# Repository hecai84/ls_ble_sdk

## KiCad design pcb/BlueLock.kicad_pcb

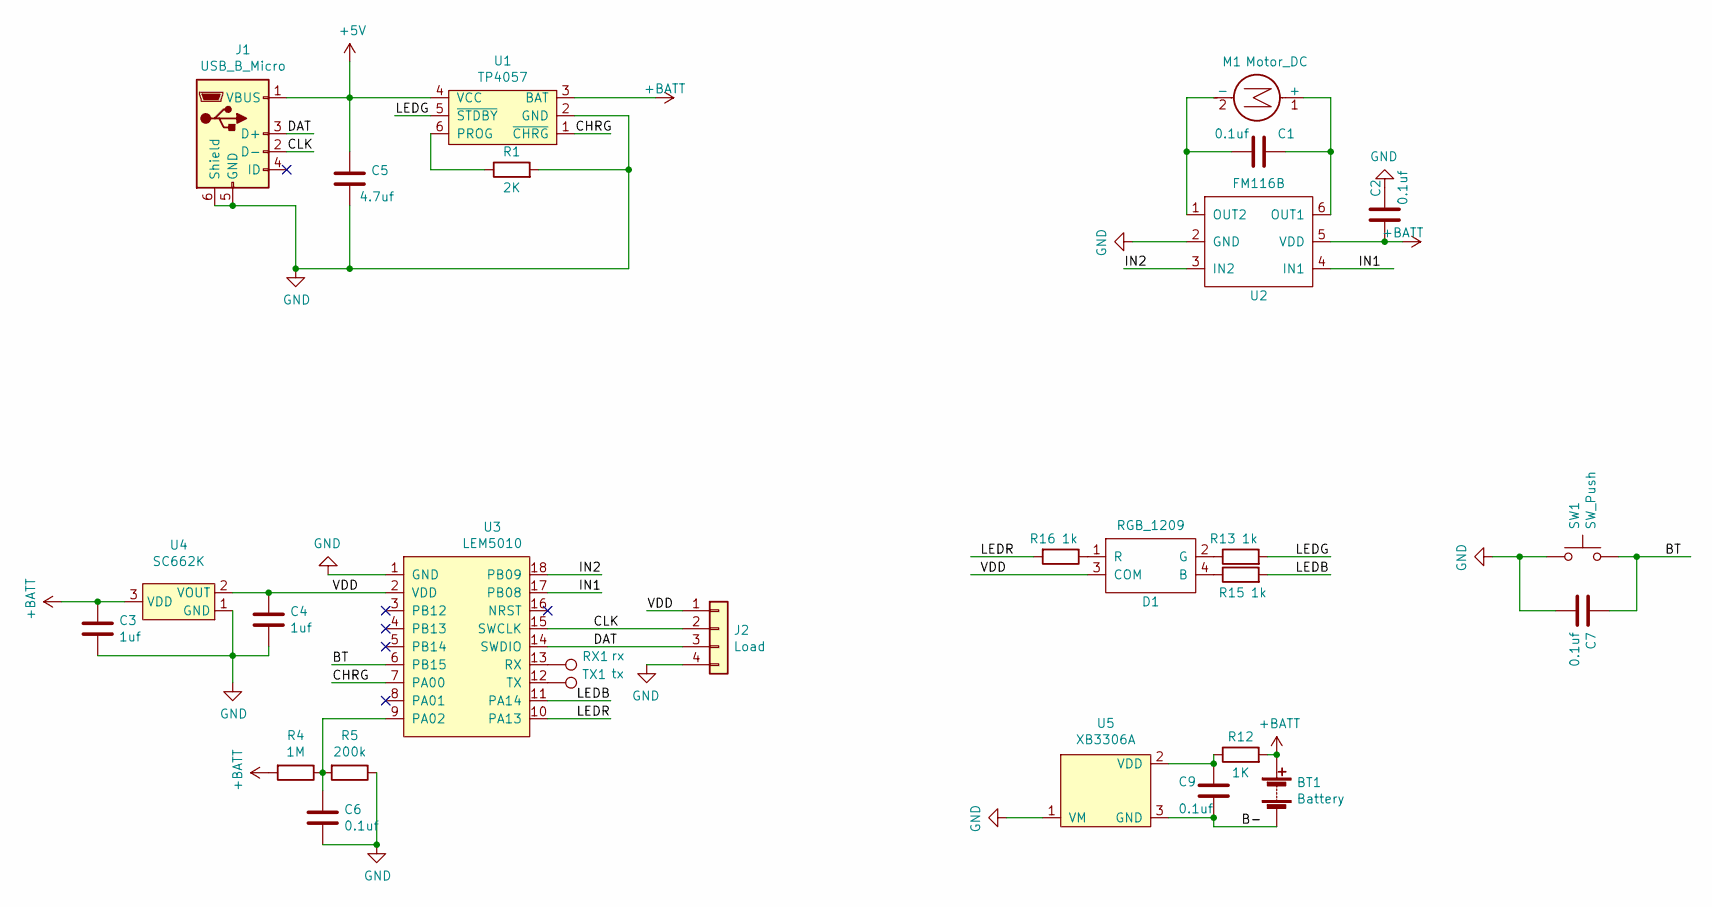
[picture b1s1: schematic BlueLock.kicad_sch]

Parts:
BT1: Battery; Pin_2_wide
C1, C2, C6, C7, C9: 0.1uf; C_0603_1608Metric
C3, C4: 1uf; C_0603_1608Metric
C5: 4.7uf; C_0603_1608Metric
D1: RGB_1209
J1: USB_B_Micro; USB_Micro-B_Molex-105017-0001
J2: Load; PinHeader_1x04_P2.54mm_Vertical
M1: Motor_DC; Pin_2_wide
R1: 2K; R_0603_1608Metric
R4: 1M; R_0603_1608Metric
R5: 200k; R_0603_1608Metric
R12: 1K; R_0603_1608Metric
R13, R15, R16: 1k; R_0603_1608Metric
RX1: rx; TestPoint_Pad_1.0x1.0mm
SW1: SW_Push; SW_6x6
TX1: tx; TestPoint_Pad_1.0x1.0mm
U1: TP4057; SOT-23-6
U2: FM116B; SOT-23-6
U3: LEM5010
U4: SC662K; SOT-23
U5: XB3306A; SOT-23

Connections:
+5V: C5.1, J1.1 (VBUS), U1.4 (VCC)
+BATT: BT1.1 (+), C2.1, C3.1, R4.2, R12.2, U1.3 (BAT), U2.5 (VDD), U4.3 (VDD)
/B-: BT1.2 (-), C9.2, U5.3 (GND)
/BT: C7.1, SW1.2, U3.6 (PB15)
/CHRG: U1.1 (~CHRG), U3.7 (PA00)
/CLK: J1.2 (D-), J2.2, U3.15 (SWCLK)
/DAT: J1.3 (D+), J2.3, U3.14 (SWDIO)
/IN1: U2.4 (IN1), U3.17 (PB08)
/IN2: U2.3 (IN2), U3.18 (PB09)
/LEDB: R15.2, U3.11 (PA14)
/LEDG: R13.2, U1.5 (~STDBY)
/LEDR: R16.2, U3.10 (PA13)
/VDD: C4.1, D1.3 (COM), J2.1, U3.2 (VDD), U4.2 (VOUT)
GND: C2.2, C3.2, C4.2, C5.2, C6.2, C7.2, J1.5 (GND), J1.6 (Shield), J2.4, R1.2, R5.1, SW1.1, U1.2 (GND), U2.2 (GND), U3.1 (GND), U4.1 (GND), U5.1 (VM)
unnamed: C1.1, M1.1 (+), U2.6 (OUT1)
unnamed: C1.2, M1.2 (-), U2.1 (OUT2)
unnamed: C6.1, R4.1, R5.2, U3.9 (PA02)
unnamed: C9.1, R12.1, U5.2 (VDD)
unnamed: D1.1 (R), R16.1
unnamed: D1.2 (G), R13.1
unnamed: D1.4 (B), R15.1
unnamed: R1.1, U1.6 (PROG)
unnamed: RX1.1, U3.13 (RX)
unnamed: TX1.1, U3.12 (TX)

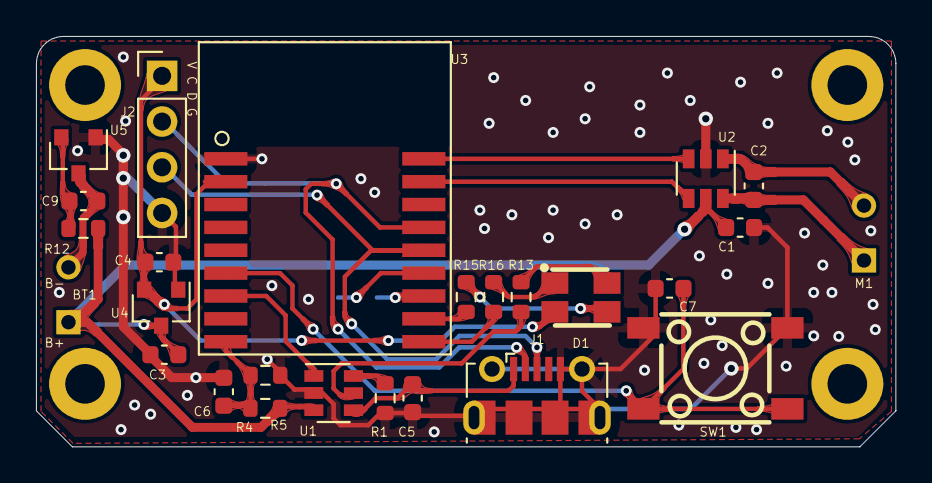
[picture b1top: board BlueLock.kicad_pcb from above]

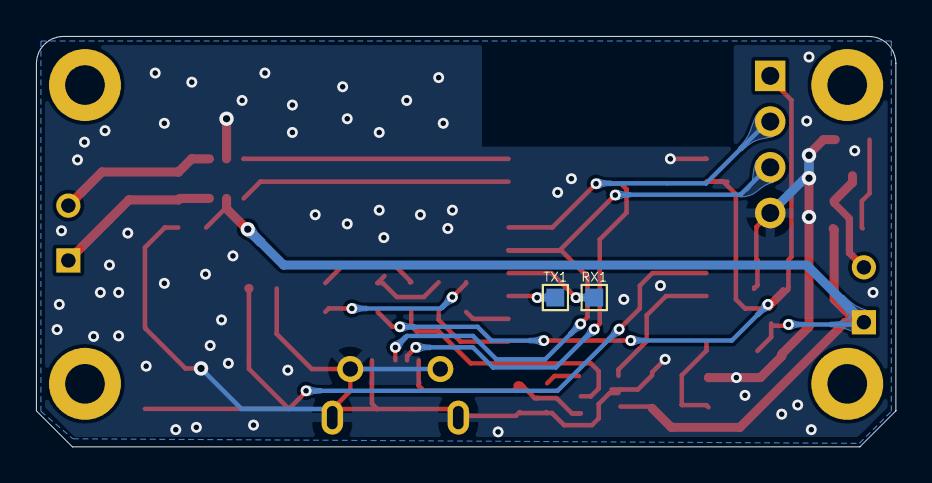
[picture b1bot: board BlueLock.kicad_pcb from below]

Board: 2 copper layers, 47.7 x 22.8 mm, 32 parts (2 on the bottom side), 24 nets.

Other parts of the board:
0, 0#2, 0#3, 0#4: R2R4

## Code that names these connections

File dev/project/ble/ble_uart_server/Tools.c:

/*
 * @Description:
 * @Author: hecai
 * @Date: 2021-09-16 10:44:14
 * @LastEditTime: 2023-03-15 11:43:16
 * @FilePath: \ls_ble_sdk\dev\project\ble\ble_uart_server\Tools.c
 */
#include "Tools.h"
#include "lscrypt.h"
#include "lsadc.h"
#include <string.h>
#include "flash.h"
/**buff**/
uint8_t ciphertext_buff[64];
uint8_t plaintext_buff[64];
extern u8 pw[];
extern u8 lastTime[];

#define BT PB15
#define CHRG PA00
#define LED_RED PA14
#define LED_BLUE PA13
#define TWINK_BLUE_TIME 500
#define TWINK_RED_TIME1 500
#define TWINK_RED_TIME2 1500
#define LONGPRESS_TIME 3000
#define CHRG_OVERTIME 500
#define REFRESH_VBAT_TIME 60000

static struct builtin_timer *led_timer_blue = NULL;
static struct builtin_timer *led_timer_red = NULL;
static struct builtin_timer *click_timer = NULL;
static struct builtin_timer *chrg_timer = NULL;
static u8 twinkRedTimes;
static u8 twinkBlueTimes;
volatile uint8_t recv_flag = 1;
ADC_HandleTypeDef hadc;
u8 battery = 5;
u8 redState = 1;
#include "main.h"

void Error_Handler(void);

void initLed(void)
{
    io_cfg_output(LED_RED); // LEDR
    // io_cfg_opendrain(LED_RED);
    io_write_pin(LED_RED, 1);
    io_cfg_output(LED_BLUE); // LEDB
    // io_cfg_opendrain(LED_BLUE);
    io_write_pin(LED_BLUE, 1);
}

/*
在LE501X系统中，只有PA00、PA07、PB11、PB15四个IO可以在任
意状态下触发中断，其余IO只能在CPU工作状态下触发中断，不能在BLE休眠状态下触发中断。
BLE处于广播或者连接时，系统根据广播、连接的间隔定期自动休眠、唤醒，所以这种应用场景，
建议使用上述四根IO作为中断。
*/
void initExti(void)
{
    io_cfg_input(BT);                     // PB11 config input
    io_pull_write(BT, IO_PULL_UP);        // PB11 config pullup
    io_exti_config(BT, INT_EDGE_FALLING); // PB11 interrupt falling edge
    io_exti_enable(BT, true);             // PB11 interrupt enable

    io_cfg_input(CHRG);                     // PB11 config input
    io_pull_write(CHRG, IO_PULL_UP);        // PB11 config pullup
    io_exti_config(CHRG, INT_EDGE_FALLING); // PB11 interrupt falling edge
    io_exti_enable(CHRG, true);             // PB11 interrupt enable
}

void toggleRed(void *param)
{
    if (twinkRedTimes != 255)
        twinkRedTimes--;
    redState = !redState;
    io_write_pin(LED_RED, redState);
    if (led_timer_red && twinkRedTimes > 0)
    {
        if (redState == 0)
        {
            builtin_timer_start(led_timer_red, TWINK_RED_TIME1, NULL);
        }
        else
        {
            builtin_timer_start(led_timer_red, TWINK_RED_TIME2, NULL);
        }
    }
}
void toggleBlue(void *param)
{
    twinkBlueTimes--;
    io_toggle_pin(LED_BLUE);
    if (led_timer_blue && twinkBlueTimes > 0)
    {
        builtin_timer_start(led_timer_blue, TWINK_BLUE_TIME, NULL);
    }
    else
    {
        io_write_pin(LED_BLUE, 1);
    }
}
void longPress(void *param)
{
    if (io_read_pin(BT) == 0)
    {
        LOG_I("longPress");
        SetLedBlue(LED_TWINK);
        memcpy(pw, DEFAULT_PW, 16);
        LOG_I("new pw:%s", pw);
        memset(lastTime, 0, 11);
        writeFlash(RECODE_PW, pw, 16);
    }
}
void chrgcheck(void *param)
{
    if (io_read_pin(CHRG) == 0)
    {
        SetLedRed(LED_OPEN);
        if (chrg_timer)
            builtin_timer_start(chrg_timer, CHRG_OVERTIME, NULL);
    }
    else
    {
        LOG_I("charge out");
        UpdateBattery();
        updateAdv();
        SetLedRed(LED_CLOSE);
    }
}

void lsadc_init(void)
{
    /** Common config  */
    hadc.Instance = LSADC;
    hadc.Init.DataAlign = ADC_DATAALIGN_RIGHT;
    hadc.Init.ScanConvMode = ADC_SCAN_DISABLE; /* Sequencer disabled (ADC conversion on only 1 channel: channel set on rank 1) */
    hadc.Init.NbrOfConversion = 1;             /* Parameter discarded because sequencer is disabled */
    hadc.Init.DiscontinuousConvMode = DISABLE; /* Parameter discarded because sequencer is disabled */
    hadc.Init.NbrOfDiscConversion = 1;         /* Parameter discarded because sequencer is disabled */

    hadc.Init.ContinuousConvMode = ENABLE;           /* Continuous mode to have maximum conversion speed (no delay between conversions) */
    hadc.Init.TrigType = ADC_REGULAR_SOFTWARE_TRIGT; /* Trig of conversion start done by which event */
    hadc.Init.Vref = ADC_VREF_INSIDE;
}

void HAL_ADC_ConvCpltCallback(ADC_HandleTypeDef *h)
{
    u16 value;
    // 1400/4095*6
    value = HAL_ADC_GetValue(h) * 2.051;
    LOG_I("battery:%d", value);
    if (value < 3200)
    {
        LOG_I("twink red");
        SetLedRed(LED_TWINK);
    }
    else if (io_read_pin(CHRG) != 0)
    {
        SetLedRed(LED_CLOSE);
    }
    // 3*1400*adc_value/4095
    if (value > 3950)
        battery = 5;
    else if (value > 3800)
        battery = 4;
    else if (value > 3600)
        battery = 3;
    else if (value > 3400)
        battery = 2;
    else
        battery = 1;
    recv_flag = 1;
    adc12b_in6_io_deinit();
    HAL_ADC_Stop_IT(h); // close adc per
    HAL_ADC_DeInit(h);
    //如果电量有变化，重新检查是否有变化
}

void UpdateBattery(void)
{
    if (1)
    {
        if (HAL_ADC_Init(&hadc) != HAL_OK)
        {
            LOG_I("HAL_ADC_Init error");
            Error_Handler();
        }

        ADC_ChannelConfTypeDef sConfig = {0};
        /**
         * Configure Regular Channel
         */
        sConfig.Channel = ADC_CHANNEL_6;
        sConfig.Rank = ADC_REGULAR_RANK_1;
        sConfig.SamplingTime = 0x00000002U;
        if (HAL_ADC_ConfigChannel(&hadc, &sConfig) != HAL_OK)
        {
            Error_Handler();
        }
        adc12b_in6_io_init();
        recv_flag = 0;
        LOG_I("HAL_ADC_Start_IT");
        HAL_ADC_Start_IT(&hadc);
    }

    // if (recv_flag == 1)
    // {
    //     recv_flag = 0;
    //     HAL_ADC_Start_IT(&hadc);
    // }
}

void SetLedRed(LED_STATE state)
{
    twinkRedTimes = 255;
    if (state == LED_TWINK)
    {
        LOG_I("SetLedRed TWINK");
        if (led_timer_red == NULL)
        {
            led_timer_red = builtin_timer_create(toggleRed);
        }
        io_write_pin(LED_RED, 0);
        redState = 0;
        LOG_I("star SetLedRed TWINK");
        builtin_timer_start(led_timer_red, 500, NULL);
    }
    else
    {
        if (led_timer_red != NULL)
        {
            builtin_timer_stop(led_timer_red);
        }
        if (state == LED_OPEN)
            io_write_pin(LED_RED, 0);
        if (state == LED_CLOSE)
            io_write_pin(LED_RED, 1);
    }
}

void SetLedBlue(LED_STATE state)
{
    if (state == LED_TWINK)
    {
        twinkBlueTimes = 10;
        LOG_I("SetLedBlue TWINK");
        if (led_timer_blue == NULL)
            led_timer_blue = builtin_timer_create(toggleBlue);
        io_write_pin(LED_BLUE, 0);
        builtin_timer_start(led_timer_blue, TWINK_BLUE_TIME, NULL);
    }
    else
    {
        if (state == LED_OPEN)
        {
            LOG_I("SetLedBlue OPEN");
            io_write_pin(LED_BLUE, 0);
        }
        if (state == LED_CLOSE)
        {
            LOG_I("SetLedBlue CLOSE");
            io_write_pin(LED_BLUE, 1);
        }
    }
}

void io_exti_callback(uint8_t pin)
{
    LOG_I("exti");
    switch (pin)
    {
    case BT:
        // do something

        LOG_I("click");
        if (click_timer == NULL)
        {
            // builtin_timer_stop(click_timer);
            click_timer = builtin_timer_create(longPress);
        }
        builtin_timer_stop(click_timer);
        builtin_timer_start(click_timer, LONGPRESS_TIME, NULL);
        break;
    case CHRG:
        LOG_I("charging");
        battery=6;
        updateAdv();
        SetLedRed(LED_OPEN);
        if (chrg_timer == NULL)
        {
            chrg_timer = builtin_timer_create(chrgcheck);
        }
        builtin_timer_stop(chrg_timer);
        builtin_timer_start(chrg_timer, CHRG_OVERTIME, NULL);
        break;
    default:
        break;
    }
}
/**
 * @brief  This function is executed in case of error occurrence.
 * @retval None
 */
void Error_Handler(void)
{
    /* USER CODE BEGIN Error_Handler_Debug */
    /* User can add his own implementation to report the HAL error return state */

    /* USER CODE END Error_Handler_Debug */
}

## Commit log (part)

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2021-07-20 dev/soc/sagi: change sram addr and fix .h file error
    Test Plan: NO
    Reviewers: jwzhang, mingzhou, xtzhang
    Reviewed By: xtzhang
    Differential Revision: http://10.10.20.8/D958
2021-07-22 le501x: stack&platform update for ali os sleep
    Test Plan: No
    Reviewers: jwzhang, mingzhou
    Reviewed By: jwzhang
    Differential Revision: http://10.10.20.8/D962
2021-07-26 tinyfs: tinyfs gc & erase strategy update
    Test Plan: No
    Reviewers: jwzhang, mingzhou
    Reviewed By: jwzhang, mingzhou
    Differential Revision: http://10.10.20.8/D960
2021-07-26 module/static_buffer: remove remainder operator from dword fifo put get
    Test Plan: No
    Reviewers: jwzhang, mingzhou
    Reviewed By: mingzhou
    Differential Revision: http://10.10.20.8/D963
2021-07-26 peripheral/spi_flash: spi_flash_dual_xip_mode_exit bug fix
    Test Plan: No
    Reviewers: jwzhang, mingzhou
    Reviewed By: mingzhou
    Differential Revision: http://10.10.20.8/D964
2021-08-02 tinyfs: tail section nvm read bug fix
    Test Plan: No
    Reviewers: jwzhang, mingzhou
    Reviewed By: jwzhang
    Differential Revision: http://10.10.20.8/D966
2021-08-03 le501x: sw_timer for mcu only
    Test Plan: No
    Reviewers: jwzhang, mingzhou
    Reviewed By: jwzhang
    Differential Revision: http://10.10.20.8/D965
2021-08-03 le501x: mcu mode sw timer bug fix
    Test Plan: No
    Reviewers: jwzhang, mingzhou
    Reviewed By: jwzhang
    Differential Revision: http://10.10.20.8/D968
2021-08-03 tools/mdk.py: add CPPDEFINES to keil CDefines
    Test Plan: No
    Reviewers: jwzhang, mingzhou
    Reviewed By: jwzhang
    Differential Revision: http://10.10.20.8/D971
2021-08-04 le501x: do not block due to lsi freq counting before sleep
    Test Plan: No
    Reviewers: jwzhang, mingzhou
    Reviewed By: jwzhang
    Differential Revision: http://10.10.20.8/D970
2021-08-05 le501x: sleep wakeup delay update for LSI&LSE
    Test Plan: No
    Reviewers: jwzhang, mingzhou
    Reviewed By: mingzhou
    Differential Revision: http://10.10.20.8/D973
2021-08-05 le501x: aos ll stack update for ext adv
    Test Plan: No
    Reviewers: jwzhang, mingzhou
    Reviewed By: mingzhou
    Differential Revision: http://10.10.20.8/D975
2021-08-05 dev/module/ble: Fix bug for phy_type definition.
    Test Plan: no
    Reviewers: jwzhang, xtzhang
    Reviewed By: xtzhang
    Differential Revision: http://10.10.20.8/D976
2021-08-05 dev/soc/sagi: fix sagi lp0 bug - flash io pull up
    Test Plan: no
    Reviewers: jwzhang, mingzhou, xtzhang
    Reviewed By: xtzhang
    Differential Revision: http://10.10.20.8/D977
2021-08-06 update rf parameter
    Summary: Signed-off-by: lsjwzhang <jwzhang@linkedsemi.com>
    Test Plan: No
    Reviewers: mingzhou, xtzhang
    Reviewed By: xtzhang
    Differential Revision: http://10.10.20.8/D978
2021-08-06 le501x: aos stack buf config update
    Test Plan: No
    Reviewers: jwzhang, mingzhou
    Reviewed By: mingzhou
    Differential Revision: http://10.10.20.8/D979
2021-08-10 v0.9.1: tinyfs bug fix & rf param optimization
2021-08-10 module: add sw calendar
    Test Plan: No
    Reviewers: jwzhang, mingzhou
    Reviewed By: mingzhou
    Differential Revision: http://10.10.20.8/D981
2021-08-10 doc
    Test Plan: no
    Reviewers: jwzhang, mingzhou, gbzhang
    Reviewed By: jwzhang
    Differential Revision: http://10.10.20.8/D944
2021-08-11 dev/stack: Add interface for app to set passkey in DISPLAY_PASSKEY message; Delete unnecessary enumeration for slave auth.
    Test Plan: no
    Reviewers: jwzhang, xtzhang
    Reviewed By: xtzhang
    Differential Revision: http://10.10.20.8/D983
2021-08-12 module/calendar: get current internal time bug fix
    Test Plan: No
    Reviewers: jwzhang, mingzhou
    Reviewed By: mingzhou
    Differential Revision: http://10.10.20.8/D984
2021-08-13 taurus: usb type def and usb io func
    Test Plan: No
    Reviewers: jwzhang, mingzhou
    Reviewed By: jwzhang
    Differential Revision: http://10.10.20.8/D985
2021-08-13 dev/soc/gemini:updata boot_rom.rst.txt -add sync word and flash init cmd
    Test Plan: no
    Reviewers: jwzhang, mingzhou, xtzhang
    Reviewed By: xtzhang
    Differential Revision: http://10.10.20.8/D986
2021-08-13 spi_flash: do_spi_flash_program_svcall prototype error fix
    Test Plan: No
    Reviewers: jwzhang, mingzhou
    Reviewed By: mingzhou
    Differential Revision: http://10.10.20.8/D987
2021-08-14 dev\example\peripheral\rtc: Modify RTC driver according to the latest RC configuration.
    Test Plan: no
    Reviewers: jwzhang, xtzhang
    Reviewed By: jwzhang
    Differential Revision: http://10.10.20.8/D990
2021-08-17 module/common: cdll_insert bug fix
    Test Plan: No
    Reviewers: jwzhang, mingzhou
    Reviewed By: mingzhou
    Differential Revision: http://10.10.20.8/D991
2021-08-17 lsqspiv2:write data bug fix & cdll: insert bug fix
    Test Plan: No
    Reviewers: jwzhang, mingzhou
    Reviewed By: mingzhou
    Differential Revision: http://10.10.20.8/D992
2021-08-17 lsqspiv2: clr fsm_end int before read_write
    Test Plan: No
    Reviewers: jwzhang, mingzhou
    Reviewed By: mingzhou
    Differential Revision: http://10.10.20.8/D993
2021-08-18 module/calendar: arm nanolib compatibility
    Test Plan: No
    Reviewers: jwzhang, mingzhou
    Reviewed By: mingzhou
    Differential Revision: http://10.10.20.8/D994
2021-08-18 doc\rtc: Update docs for RTC.
    Test Plan: no
    Reviewers: jwzhang, xtzhang
    Reviewed By: xtzhang
    Differential Revision: http://10.10.20.8/D996
2021-08-18 lsqspiv2: stg command without data bug fix
    Test Plan: No
    Reviewers: jwzhang, mingzhou
    Reviewed By: mingzhou
    Differential Revision: http://10.10.20.8/D995
2021-08-19 fixed rf power for lp0 mode
    Summary: Signed-off-by: lsjwzhang <jwzhang@linkedsemi.com>
    Test Plan: No
    Reviewers: mingzhou, xtzhang
    Reviewed By: mingzhou
    Differential Revision: http://10.10.20.8/D997
2021-08-19 add mesh provisioner role
    Summary: Signed-off-by: lsjwzhang <jwzhang@linkedsemi.com>
    Test Plan: No
    Reviewers: mingzhou, xtzhang
    Reviewed By: xtzhang
    Differential Revision: http://10.10.20.8/D1000
2021-08-20 dev\module\tinyfs: Fix bug in tinyfs_list_init.
    Test Plan: no
    Reviewers: jwzhang, xtzhang
    Reviewed By: xtzhang
    Differential Revision: http://10.10.20.8/D1001
2021-08-20 sw_timer: 32bit int overflow bug fix
    Test Plan: No
    Reviewers: jwzhang, mingzhou
    Reviewed By: mingzhou
    Differential Revision: http://10.10.20.8/D1002
2021-08-20 doc: update adc jpg file name
    Test Plan: No
    Reviewers: jwzhang, mingzhou
    Reviewed By: mingzhou
    Differential Revision: http://10.10.20.8/D1003
2021-08-21 sw_timer: wkup compensation var overflow bug fix; examples: add software calendar demo
    Test Plan: No
    Reviewers: jwzhang, mingzhou
    Reviewed By: mingzhou
    Differential Revision: http://10.10.20.8/D1004
2021-08-21 2.4G: Add support for 2Mbps PHY.
    Test Plan: no
    Reviewers: jwzhang, xtzhang
    Reviewed By: xtzhang
    Differential Revision: http://10.10.20.8/D1008
2021-08-21 fixed model subscribe in genie mesh
    Summary: Signed-off-by: lsjwzhang <jwzhang@linkedsemi.com>
    Test Plan: No
    Reviewers: mingzhou, xtzhang
    Reviewed By: xtzhang
    Differential Revision: http://10.10.20.8/D1010
2021-08-23 doc: Update doc for ble_single_role
    Test Plan: no
    Reviewers: jwzhang, xtzhang
    Reviewed By: xtzhang
    Differential Revision: http://10.10.20.8/D1012
2021-08-24 module/calendar: alarm re-sched if base timer wrap
    Test Plan: No
    Reviewers: jwzhang, mingzhou
    Reviewed By: jwzhang
    Differential Revision: http://10.10.20.8/D1013
2021-08-24 dev/soc/taurus:add trng and change rf_reg base addr,add info_sbl_merger uart_cmd_mask
    Test Plan: no
    Reviewers: jwzhang, mingzhou, xtzhang
    Reviewed By: xtzhang
    Differential Revision: http://10.10.20.8/D1014
2021-08-26 gemini: micro-ecc added & qspiv2, sha bug fix
    Test Plan: No
    Reviewers: jwzhang, mingzhou
    Reviewed By: jwzhang
    Differential Revision: http://10.10.20.8/D1015
2021-08-26 dev\examples\master_slave_combine: Add dev_addr_type in start_init.
    Test Plan: no
    Reviewers: jwzhang, xtzhang
    Reviewed By: xtzhang
    Differential Revision: http://10.10.20.8/D1016
2021-08-27 sha: bug fix
    Test Plan: No
    Reviewers: jwzhang, mingzhou
    Reviewed By: mingzhou
    Differential Revision: http://10.10.20.8/D1018
2021-08-27 gemini: boot_rom to
    Test Plan: No
    Reviewers: jwzhang, mingzhou
    Reviewed By: mingzhou
    Differential Revision: http://10.10.20.8/D1020
2021-08-28 peripheral: add lscrc
    Test Plan: No
    Reviewers: jwzhang, mingzhou
    Reviewed By: mingzhou
    Differential Revision: http://10.10.20.8/D1025
2021-08-28 dev\module\ble: Add adv report parsing API.
    Test Plan: no
    Reviewers: jwzhang, xtzhang
    Reviewed By: xtzhang
    Differential Revision: http://10.10.20.8/D1024
2021-08-30 dev/module/ble: Delete unnecessary header file.
    Test Plan: no
    Reviewers: jwzhang, xtzhang
    Reviewed By: xtzhang
    Differential Revision: http://10.10.20.8/D1028
2021-08-30 le501x: ll stack for aos build with -flto
    Test Plan: No
    Reviewers: jwzhang, mingzhou
    Reviewed By: mingzhou
    Differential Revision: http://10.10.20.8/D1022
2021-09-17 实现蓝牙控制电机正反转
2021-09-29 基本功能实现
2021-09-29 添加pcb文件
2021-12-06 systick: Fix bug in systick in 0.9.1
2021-12-06 meshlib: Update libmesh.o
2021-12-06 spi_flash: Delete unnecessary log in spi_flash.c
2021-12-07 examples\ble\at_proj:remove gattc_get_mtu func,update rfpower set
    Summary:
    Test Plan:
    NO
    Reviewers:
    Subscribers:
2021-12-07 gpio pushpull bug fix
2021-12-07 peripheral/gpio: add ble=false in sconsscript
2021-12-07 modem_rf_le501x: fixed rf power during wakeup in sleep mode
    Summary: Signed-off-by: lsjwzhang <jwzhang@linkedsemi.com>
    Test Plan:
    No
    Reviewers:
    Subscribers:
2021-12-07 Perpheral:SPI:Fix spi tx single 8-bit or 16-bit data bug; Modify SPI data transform process;
2021-12-07 Sleep:Exti:Fix not entering exti callback somteimes when DEEP SLEEP enable Fix this by enable exti before WFI.
2021-12-07 UART:io_config:Enable UART RX Io pull-up. Config UART RX io pull-up.
2021-12-07 Examples:Adc single channel:Modify adc clock div. Increase adc clock div to improve accuracy.
2021-12-08 Examples:UART RX:Enable uart rx io_pull_up Update uart rx config
2021-12-08 build error fix
2021-12-09 peripheral/pdm ：build error fix
2021-12-10 ota: Fix bug in boot ram & flash with updated systick.
2021-12-13 distance_detect: Add demo for distance detect.
2021-12-16 tinyfs merge
2021-12-18 IIC & sleep: 1. Add systick_stop in deep sleep to fix bug of entering sleep. 2.Update IIC driver to the latest version in gitlab.
2021-12-18 Add pcm play for rssi distance detect. Modify bug in dmac_config.h
2021-12-21 Add keywords "volatile" to variables
2021-12-22 fix build warning
2021-12-23 ssi_test: Update ssi test demo.
2021-12-25 Peripheral:spi:Update systick poll time and rx handler
2021-12-30 修改指令
2021-12-31 lsi counting sync & check
2021-12-31 stack: lib update
2021-12-31 bootram: fix bug holding fault function
2022-01-01 spi_flash: Fix bug when a flash suspend comes immediately after a flash resume in BLE_Handler
2022-01-01 sleep: Increate delay in wait_dpll_lock
2022-01-01 flash: Update flash driver with the latest version in gitlab
2022-01-05 keil proj update
2022-01-07 binary update for builtin_timer
2022-01-10 正式版本1.0 1.开启低功耗。 2.完善逻辑
2022-01-25 1.更新低电量检测 2.拔电更新电量
2022-02-15 更新pcb
2022-02-15 单电池,不升压版本.
2022-02-15 1.修改电池电压检测, 2.修改电机控制
2022-02-21 tinyfs gc condition update
2022-02-21 sleep leakage caused by adc
2022-02-22 Update RTC.
2022-02-22 examples\at_proj: update rtc wkup time
2022-06-27 蓝牙共享电池分支
2022-07-31 添加生产文件
2022-08-27 添加关闭的时间控制
2022-11-30 添加一个固定时间戳
2023-01-12 修改固定时间的位数不对的问题
2023-03-15 v1.3版，修改开门控制方式，长按闪灯次数改为5次。
